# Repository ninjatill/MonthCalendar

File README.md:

# Month Calendar
A daily gold star system, one month at a time. Inspired by the [Every Day Calendar](https://www.kickstarter.com/projects/simonegiertz/the-every-day-calendar), this is a compact version that has 48 total touch pads.

I saw the Every Day Calendar (EDC) referenced on the Particle forums. It sounded like a great idea and I needed way to track if I took my daily allergy pill. However, the EDC is very large and therefore expensive to manufacture. It is also a big challenge (and cost) to read 365 touch inputs and control 365 LEDs (especially if made to be RGB or varying intensity). I also thought the functionality could be expanded beyond just turning an LED on to indicate completion. By the time I got around to designing my own version, the Kickstarter campain had closed and there were no resouces made available via open source yet. So I designed it all from scratch.

My Design Criteria:
- Should be small enough to fit inside a medicine cabinet or mounted on limited wall space in a bathroom.
- Should still be able to track every day of the year.
- Should record and track progress and report it to the cloud for review.
- Should be able to track multiple users (like a husband and wife pair).
- Should use capacitive touch (seems more robust and it's something new to learn).
- Should have colored LEDs that shine up through the PCB (similar to the static LED color on the EDC). Color can be used for:
  - Indicating missed days with red (or some alternative) color.
  - Showing fancy animations to entice interaction/completion.
  - Indicating separate users and tasks via differing color schemes.

Additional considerations (some after starting the design):
- There's no need to have the LEDs on all the time. Perhaps some sort of human presense detector can be incorporated to only turn on the LEDs when someone is near the system.
- If this is in a bathroom, where most people start their day, it would be benificial to act as a calendar to indicate what is the current day.
- Because of the modularity, the top touch plate (described below) could be swapped out for different configurations or locales. It might be a benifit (or neccessary) to add non-volitile storage to the touch plate to identify hardware revisions, serial numbers, locales, layout changes, etc.
- To minimize light bleed between indicators I will fabricate a 3D-printed light collimator.
- Neopixels are the obvious choice for RGB LEDs because they are chainable and have their own internal controller. I think the RGBW chips would be best so you can stil get the white LED "classic" look. Each RGBW Neopixel can draw up to 80 mA and with 48 Neopixels, the max current draw is 3.82 A. If adding day of week indicators, then with 53 Neopixels the current max current draw is up to 4.24 A. Although real-world applications would probably not push more than 2 A, the power draw is still significant and the power supply will have to be chosen appropriately. Additionally, there may have to be firmware constraints in place to prevent over taxing the power supply.

The initial design uses 2 PCBs connected via pin headers. The bottom PCB contains all the controller hardware and LEDs. The Top PCB is merely a touch plate containing all the capacitive touch pads. The microcontroller is inserted on the back-side of the controller PCB as well as the power entry ports. The PCBs will be mounted in a 3D printed case. 

# WARNING: This project is in development!
### Only v0.x files have been uploaded for review and all designs are subject to change without notice.

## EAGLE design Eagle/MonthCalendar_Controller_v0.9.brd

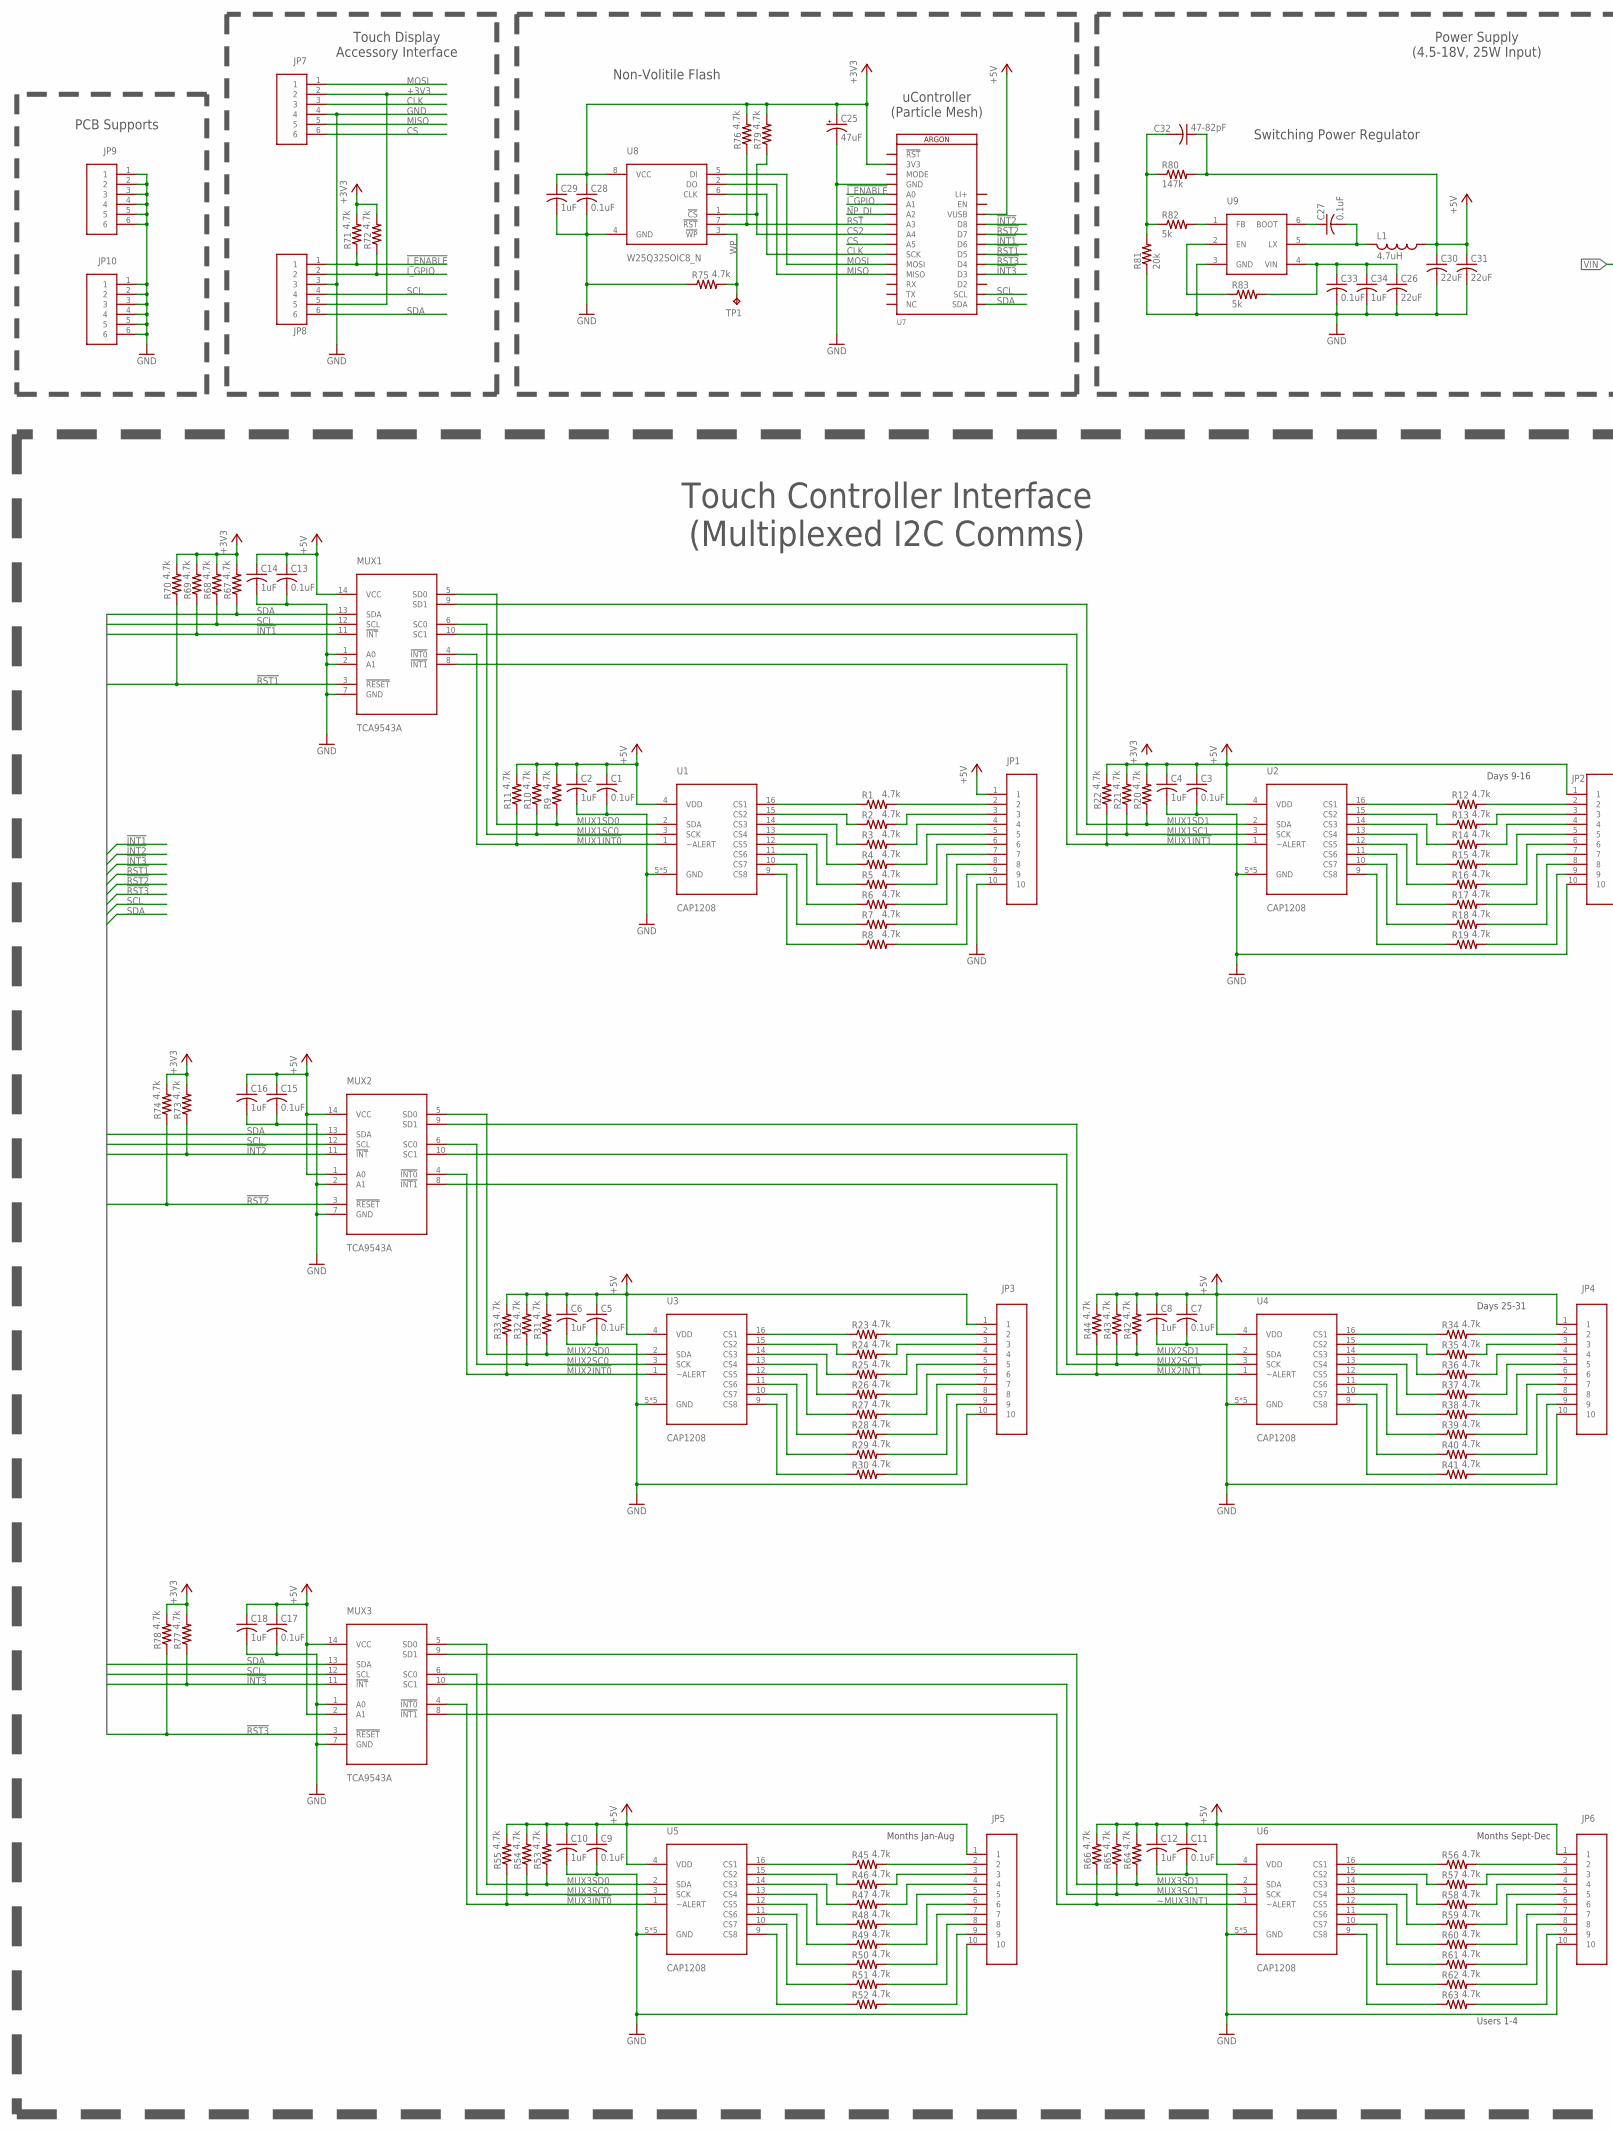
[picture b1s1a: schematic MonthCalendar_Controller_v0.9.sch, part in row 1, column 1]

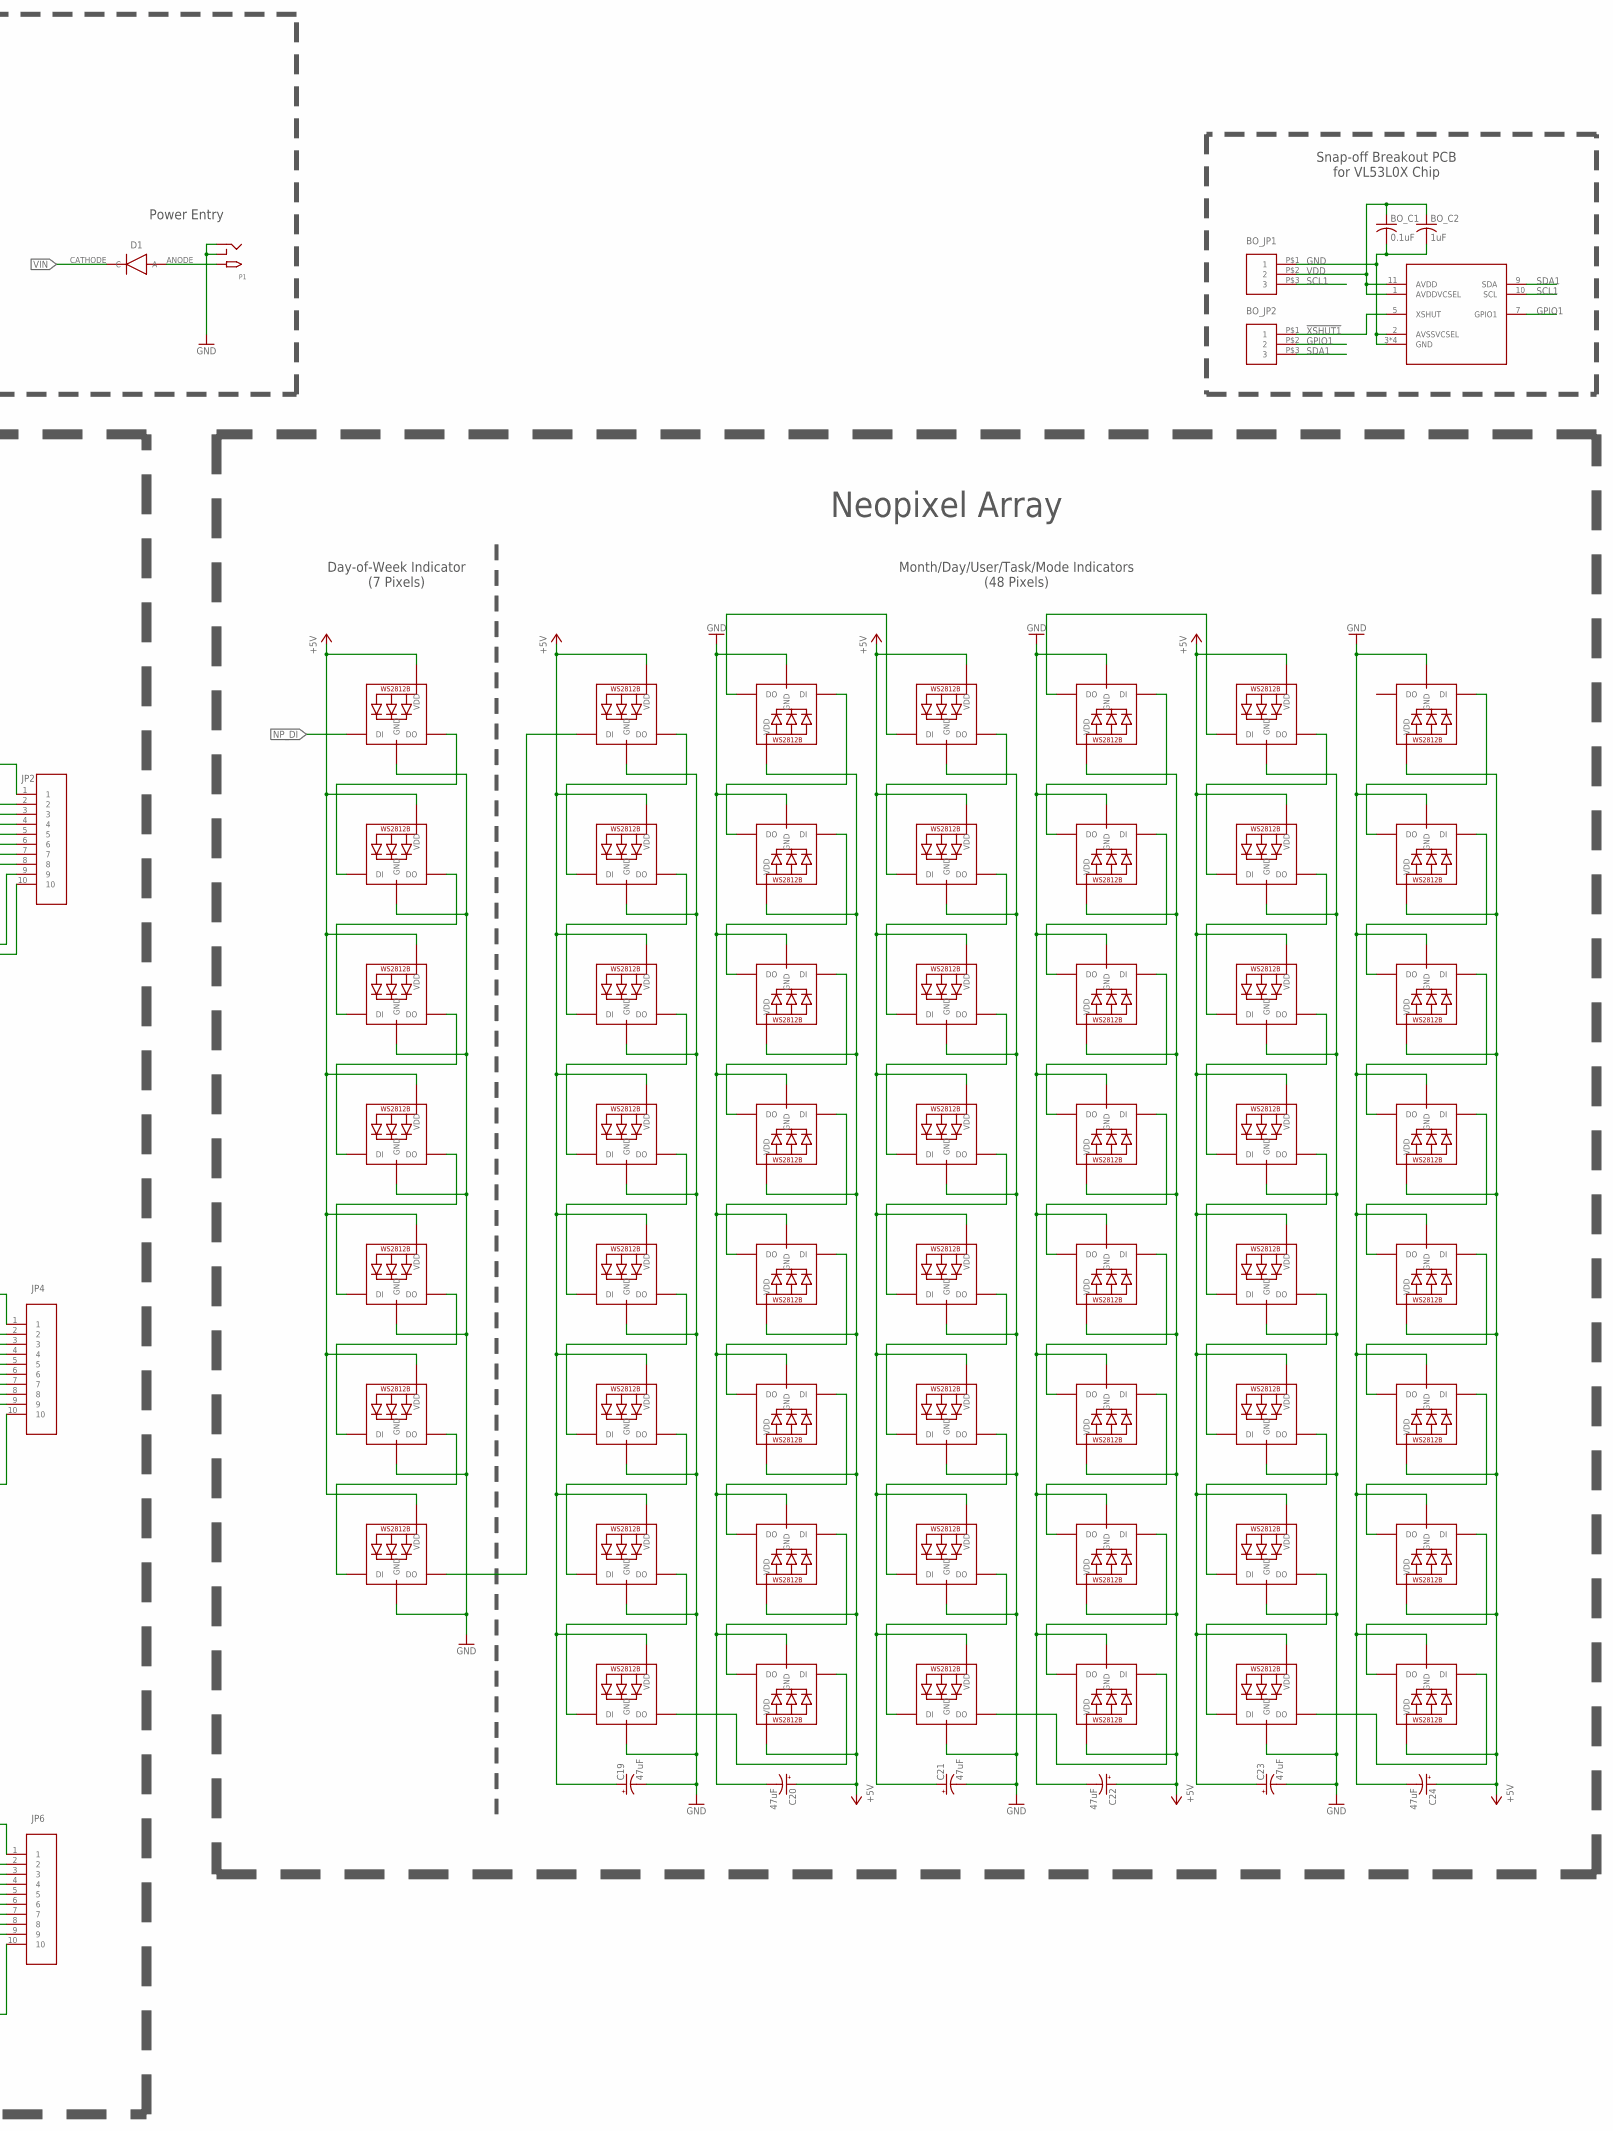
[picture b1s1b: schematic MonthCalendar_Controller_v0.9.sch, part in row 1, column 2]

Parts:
BO_C1: 0.1uF; C0603
BO_C2: 1uF; C0603
BO_JP1, BO_JP2: PINHEAD_1X350MIL; PINHEAD_1X3_50MIL
BO_U1: VL53L0X
C1, C3, C5, C7, C9, C11, C13, C15, C17, C27, C28, C33: 0.1uF; C0603
C2, C4, C6, C8, C10, C12, C14, C16, C18, C29, C34: 1uF; C0603
C19, C20, C21, C22, C23, C24, C25: 47uF; EIA3216
C26, C30, C31: 22uF; C1206
C32: 47-82pF; C0603
D1: DIODE; SOD-128
JP1, JP2, JP3, JP4, JP5, JP6: CON_10POS_1ROWHARWIN_M3531042; CON_PINHEADER_10P_1R_TH_HARWIN_M50-3531042
JP7, JP8, JP9, JP10: CON_6POS_1ROW6P1R_M50_35306; CON_PINHEADER_6P_1R_TH_HARWIN_M50-3530642
L1: 4.7uH; 0207/5V
LED1, LED2, LED3, LED4, LED5, LED6, LED7, LED8, LED9, LED10, LED11, LED12, LED13, LED14, LED15, LED16, LED17, LED18, LED19, LED20, LED21, LED22, LED23, LED24, LED25, LED26, LED27, LED28, LED29, LED30, LED31, LED32, LED33, LED34, LED35, LED36, LED37, LED38, LED39, LED40, LED41, LED42, LED43, LED44, LED45, LED46, LED47, LED48, LED49, LED50, LED51, LED52, LED53, LED54, LED55: WS2812B5050; WS2812B
MUX1, MUX2, MUX3: TCA9543A; TSSOP-14
P1: 2.1MMJACKTHM; PJ-102A
R1, R2, R3, R4, R5, R6, R7, R8, R9, R10, R11, R12, R13, R14, R15, R16, R17, R18, R19, R20, R21, R22, R23, R24, R25, R26, R27, R28, R29, R30, R31, R32, R33, R34, R35, R36, R37, R38, R39, R40, R41, R42, R43, R44, R45, R46, R47, R48, R49, R50, R51, R52, R53, R54, R55, R56, R57, R58, R59, R60, R61, R62, R63, R64, R65, R66, R67, R68, R69, R70, R71, R72, R73, R74, R75, R76, R77, R78, R79: 4.7k; R0603
R80: 147k; R0603
R81: 20k; R0603
R82, R83: 5k; R0603
TP1: TPTP20SQ; TP20SQ
U1, U2, U3, U4, U5, U6: CAP1208; QFN-16-3X3
U7: ARGON
U8: W25Q32SOIC8_N; SOIC-8_NARROW
U9: RT6255AHGJ6FCT-ND; SOT-23-6

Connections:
!INT1: MUX1.11 (!INT), R69.1, U7.23 (D6)
!INT2: MUX2.11 (!INT), R73.1, U7.25 (D8)
!INT3: MUX3.11 (!INT), R77.1, U7.20 (D3)
!I_ENABLE: JP8.1, R71.1, U7.5 (A0)
!MUX1INT0: MUX1.4 (!INT0), R11.1, U1.1 (~ALERT)
!MUX1INT1: MUX1.8 (!INT1), R22.1, U2.1 (~ALERT)
!MUX2INT0: MUX2.4 (!INT0), R33.1, U3.1 (~ALERT)
!MUX2INT1: MUX2.8 (!INT1), R44.1, U4.1 (~ALERT)
!MUX3INT0: MUX3.4 (!INT0), R55.1, U5.1 (~ALERT)
!RST1: MUX1.3 (!RESET), R70.1, U7.22 (D5)
!RST2: MUX2.3 (!RESET), R74.1, U7.24 (D7)
!RST3: MUX3.3 (!RESET), R78.1, U7.21 (D4)
!XSHUT1: BO_JP2.P$1 (1), BO_U1.5 (XSHUT)
+3V3: C25.A (+), C28.1, C29.1, JP7.2, JP8.5, R67.2, R68.2, R69.2, R70.2, R71.2, R72.2, R73.2, R74.2, R76.2, R77.2, R78.2, R79.2, U7.2 (3V3), U8.8 (VCC)
+5V: C1.1, C2.1, C3.1, C4.1, C5.1, C6.1, C7.1, C8.1, C9.1, C10.1, C11.1, C12.1, C13.1, C14.1, C15.1, C16.1, C17.1, C18.1, C19.A (+), C20.A (+), C21.A (+), C22.A (+), C23.A (+), C24.A (+), C30.1, C31.1, C32.1, JP1.1, JP2.1, JP3.1, JP4.1, JP5.1, JP6.1, L1.1, LED1.1-VDD (VDD), LED2.1-VDD (VDD), LED3.1-VDD (VDD), LED4.1-VDD (VDD), LED5.1-VDD (VDD), LED6.1-VDD (VDD), LED7.1-VDD (VDD), LED8.1-VDD (VDD), LED9.1-VDD (VDD), LED10.1-VDD (VDD), LED11.1-VDD (VDD), LED12.1-VDD (VDD), LED13.1-VDD (VDD), LED14.1-VDD (VDD), LED15.1-VDD (VDD), LED16.1-VDD (VDD), LED17.1-VDD (VDD), LED18.1-VDD (VDD), LED19.1-VDD (VDD), LED20.1-VDD (VDD), LED21.1-VDD (VDD), LED22.1-VDD (VDD), LED23.1-VDD (VDD), LED24.1-VDD (VDD), LED25.1-VDD (VDD), LED26.1-VDD (VDD), LED27.1-VDD (VDD), LED28.1-VDD (VDD), LED29.1-VDD (VDD), LED30.1-VDD (VDD), LED31.1-VDD (VDD), LED32.1-VDD (VDD), LED33.1-VDD (VDD), LED34.1-VDD (VDD), LED35.1-VDD (VDD), LED36.1-VDD (VDD), LED37.1-VDD (VDD), LED38.1-VDD (VDD), LED39.1-VDD (VDD), LED40.1-VDD (VDD), LED41.1-VDD (VDD), LED42.1-VDD (VDD), LED43.1-VDD (VDD), LED44.1-VDD (VDD), LED45.1-VDD (VDD), LED46.1-VDD (VDD), LED47.1-VDD (VDD), LED48.1-VDD (VDD), LED49.1-VDD (VDD), LED50.1-VDD (VDD), LED51.1-VDD (VDD), LED52.1-VDD (VDD), LED53.1-VDD (VDD), LED54.1-VDD (VDD), LED55.1-VDD (VDD), MUX1.14 (VCC), MUX2.1 (A0), MUX2.14 (VCC), MUX3.2 (A1), MUX3.14 (VCC), R9.2, R10.2, R11.2, R20.2, R21.2, R22.2, R31.2, R32.2, R33.2, R42.2, R43.2, R44.2, R53.2, R54.2, R55.2, R64.2, R65.2, R66.2, R80.2, U1.4 (VDD), U2.4 (VDD), U3.4 (VDD), U4.4 (VDD), U5.4 (VDD), U6.4 (VDD), U7.26 (VUSB)
BOOT: C27.1, U9.6 (BOOT)
CLK: JP7.3, U7.11 (SCK), U8.6 (CLK)
CS: JP7.6, U7.10 (A5)
CS2: R79.1, U7.9 (A4), U8.1 (!CS)
EN: R83.1, U9.2 (EN)
FB: R82.2, U9.1 (FB)
GND: BO_C1.2, BO_C2.2, BO_JP1.P$1 (1), BO_U1.2 (AVSSVCSEL), BO_U1.3 (GND), BO_U1.4 (GND), BO_U1.6 (GND), BO_U1.12 (GND), C1.2, C2.2, C3.2, C4.2, C5.2, C6.2, C7.2, C8.2, C9.2, C10.2, C11.2, C12.2, C13.2, C14.2, C15.2, C16.2, C17.2, C18.2, C19.C (-), C20.C (-), C21.C (-), C22.C (-), C23.C (-), C24.C (-), C25.C (-), C26.2, C28.2, C29.2, C30.2, C31.2, C33.2, C34.2, JP1.10, JP2.10, JP3.10, JP4.10, JP5.10, JP6.10, JP7.4, JP8.3, JP9.1, JP9.2, JP9.3, JP9.4, JP9.5, JP9.6, JP10.1, JP10.2, JP10.3, JP10.4, JP10.5, JP10.6, LED1.3-GND (GND), LED2.3-GND (GND), LED3.3-GND (GND), LED4.3-GND (GND), LED5.3-GND (GND), LED6.3-GND (GND), LED7.3-GND (GND), LED8.3-GND (GND), LED9.3-GND (GND), LED10.3-GND (GND), LED11.3-GND (GND), LED12.3-GND (GND), LED13.3-GND (GND), LED14.3-GND (GND), LED15.3-GND (GND), LED16.3-GND (GND), LED17.3-GND (GND), LED18.3-GND (GND), LED19.3-GND (GND), LED20.3-GND (GND), LED21.3-GND (GND), LED22.3-GND (GND), LED23.3-GND (GND), LED24.3-GND (GND), LED25.3-GND (GND), LED26.3-GND (GND), LED27.3-GND (GND), LED28.3-GND (GND), LED29.3-GND (GND), LED30.3-GND (GND), LED31.3-GND (GND), LED32.3-GND (GND), LED33.3-GND (GND), LED34.3-GND (GND), LED35.3-GND (GND), LED36.3-GND (GND), LED37.3-GND (GND), LED38.3-GND (GND), LED39.3-GND (GND), LED40.3-GND (GND), LED41.3-GND (GND), LED42.3-GND (GND), LED43.3-GND (GND), LED44.3-GND (GND), LED45.3-GND (GND), LED46.3-GND (GND), LED47.3-GND (GND), LED48.3-GND (GND), LED49.3-GND (GND), LED50.3-GND (GND), LED51.3-GND (GND), LED52.3-GND (GND), LED53.3-GND (GND), LED54.3-GND (GND), LED55.3-GND (GND), MUX1.1 (A0), MUX1.2 (A1), MUX1.7 (GND), MUX2.2 (A1), MUX2.7 (GND), MUX3.1 (A0), MUX3.7 (GND), P1.RING, P1.RING_SW, R75.1, R81.1, U1.5 (GND), U1.6 (GND), U1.7 (GND), U1.8 (GND), U1.PAD (GND), U2.5 (GND), U2.6 (GND), U2.7 (GND), U2.8 (GND), U2.PAD (GND), U3.5 (GND), U3.6 (GND), U3.7 (GND), U3.8 (GND), U3.PAD (GND), U4.5 (GND), U4.6 (GND), U4.7 (GND), U4.8 (GND), U4.PAD (GND), U5.5 (GND), U5.6 (GND), U5.7 (GND), U5.8 (GND), U5.PAD (GND), U6.5 (GND), U6.6 (GND), U6.7 (GND), U6.8 (GND), U6.PAD (GND), U7.4 (GND), U8.4 (GND), U9.3 (GND)
GPIO1: BO_JP2.P$2 (2), BO_U1.7 (GPIO1)
I_GPIO: JP8.2, R72.1, U7.6 (A1)
LI+: U7.28 (LI+)
LX: C27.2, L1.2, U9.5 (LX)
MISO: JP7.5, U7.13 (MISO), U8.2 (DO)
MOSI: JP7.1, U7.12 (MOSI), U8.5 (DI)
MUX1SC0: MUX1.6 (SC0), R10.1, U1.3 (SCK)
MUX1SC1: MUX1.10 (SC1), R21.1, U2.3 (SCK)
MUX1SD0: MUX1.5 (SD0), R9.1, U1.2 (SDA)
MUX1SD1: MUX1.9 (SD1), R20.1, U2.2 (SDA)
MUX2SC0: MUX2.6 (SC0), R32.1, U3.3 (SCK)
MUX2SC1: MUX2.10 (SC1), R43.1, U4.3 (SCK)
MUX2SD0: MUX2.5 (SD0), R31.1, U3.2 (SDA)
MUX2SD1: MUX2.9 (SD1), R42.1, U4.2 (SDA)
MUX3SC0: MUX3.6 (SC0), R54.1, U5.3 (SCK)
MUX3SC1: MUX3.10 (SC1), R65.1, U6.3 (SCK)
MUX3SD0: MUX3.5 (SD0), R53.1, U5.2 (SDA)
MUX3SD1: MUX3.9 (SD1), R64.1, U6.2 (SDA)
unnamed: R1.1, U1.16 (CS1)
unnamed: JP1.2, R1.2
unnamed: JP1.3, R2.2
unnamed: R2.1, U1.15 (CS2)
unnamed: R3.1, U1.14 (CS3)
unnamed: R4.1, U1.13 (CS4)
unnamed: R5.1, U1.12 (CS5)
unnamed: R6.1, U1.11 (CS6)
unnamed: R7.1, U1.10 (CS7)
unnamed: R8.1, U1.9 (CS8)
unnamed: JP1.4, R3.2
unnamed: R12.1, U2.16 (CS1)
unnamed: R13.1, U2.15 (CS2)
unnamed: R14.1, U2.14 (CS3)
unnamed: R15.1, U2.13 (CS4)
unnamed: R16.1, U2.12 (CS5)
unnamed: R17.1, U2.11 (CS6)
unnamed: R18.1, U2.10 (CS7)
unnamed: R19.1, U2.9 (CS8)
unnamed: JP2.2, R12.2
unnamed: JP1.5, R4.2
unnamed: JP1.6, R5.2
unnamed: JP1.7, R6.2
unnamed: JP1.8, R7.2
unnamed: JP1.9, R8.2
unnamed: LED1.2-DOUT (DO), LED2.4-DIN (DI)
unnamed: LED2.2-DOUT (DO), LED3.4-DIN (DI)
unnamed: LED3.2-DOUT (DO), LED4.4-DIN (DI)
unnamed: JP2.3, R13.2
unnamed: JP2.4, R14.2
unnamed: JP2.5, R15.2
unnamed: JP2.6, R16.2
unnamed: JP2.7, R17.2
unnamed: JP2.8, R18.2
unnamed: JP2.9, R19.2
unnamed: LED4.2-DOUT (DO), LED5.4-DIN (DI)
unnamed: LED5.2-DOUT (DO), LED6.4-DIN (DI)
unnamed: LED6.2-DOUT (DO), LED7.4-DIN (DI)
unnamed: R23.1, U3.16 (CS1)
unnamed: R24.1, U3.15 (CS2)
unnamed: R25.1, U3.14 (CS3)
unnamed: R26.1, U3.13 (CS4)
unnamed: R27.1, U3.12 (CS5)
unnamed: R28.1, U3.11 (CS6)
unnamed: R29.1, U3.10 (CS7)
unnamed: R30.1, U3.9 (CS8)
unnamed: JP3.2, R23.2
unnamed: JP3.3, R24.2
unnamed: JP3.4, R25.2
unnamed: JP3.5, R26.2
unnamed: JP3.6, R27.2
unnamed: JP3.7, R28.2
unnamed: JP3.8, R29.2
unnamed: JP3.9, R30.2
unnamed: LED7.2-DOUT (DO), LED8.4-DIN (DI)
unnamed: LED9.2-DOUT (DO), LED10.4-DIN (DI)
unnamed: LED10.2-DOUT (DO), LED11.4-DIN (DI)
unnamed: R34.1, U4.16 (CS1)
unnamed: R35.1, U4.15 (CS2)
unnamed: R36.1, U4.14 (CS3)
unnamed: R37.1, U4.13 (CS4)
unnamed: R38.1, U4.12 (CS5)
unnamed: R39.1, U4.11 (CS6)
unnamed: R40.1, U4.10 (CS7)
unnamed: R41.1, U4.9 (CS8)
unnamed: JP4.2, R34.2
unnamed: JP4.3, R35.2
unnamed: JP4.4, R36.2
unnamed: JP4.5, R37.2
unnamed: JP4.6, R38.2
unnamed: JP4.7, R39.2
unnamed: JP4.8, R40.2
unnamed: JP4.9, R41.2
unnamed: LED11.2-DOUT (DO), LED12.4-DIN (DI)
unnamed: LED12.2-DOUT (DO), LED13.4-DIN (DI)
unnamed: LED13.2-DOUT (DO), LED14.4-DIN (DI)
unnamed: R45.1, U5.16 (CS1)
unnamed: R46.1, U5.15 (CS2)
unnamed: R47.1, U5.14 (CS3)
unnamed: R48.1, U5.13 (CS4)
unnamed: R49.1, U5.12 (CS5)
unnamed: R50.1, U5.11 (CS6)
unnamed: R51.1, U5.10 (CS7)
unnamed: R52.1, U5.9 (CS8)
unnamed: JP5.2, R45.2
unnamed: JP5.3, R46.2
unnamed: JP5.4, R47.2
unnamed: JP5.5, R48.2
unnamed: JP5.6, R49.2
unnamed: JP5.7, R50.2
unnamed: JP5.8, R51.2
unnamed: JP5.9, R52.2
unnamed: LED14.2-DOUT (DO), LED15.4-DIN (DI)
unnamed: LED15.2-DOUT (DO), LED16.4-DIN (DI)
unnamed: LED17.2-DOUT (DO), LED18.4-DIN (DI)
unnamed: R56.1, U6.16 (CS1)
unnamed: R57.1, U6.15 (CS2)
unnamed: R58.1, U6.14 (CS3)
unnamed: R59.1, U6.13 (CS4)
unnamed: R60.1, U6.12 (CS5)
unnamed: R61.1, U6.11 (CS6)
unnamed: R62.1, U6.10 (CS7)
unnamed: R63.1, U6.9 (CS8)
unnamed: JP6.2, R56.2
unnamed: JP6.3, R57.2
unnamed: JP6.4, R58.2
unnamed: JP6.5, R59.2
unnamed: JP6.6, R60.2
unnamed: JP6.7, R61.2
unnamed: JP6.8, R62.2
unnamed: JP6.9, R63.2
unnamed: LED18.2-DOUT (DO), LED19.4-DIN (DI)
unnamed: LED19.2-DOUT (DO), LED20.4-DIN (DI)
unnamed: LED20.2-DOUT (DO), LED21.4-DIN (DI)
unnamed: LED21.2-DOUT (DO), LED22.4-DIN (DI)
unnamed: LED22.2-DOUT (DO), LED23.4-DIN (DI)
unnamed: LED23.2-DOUT (DO), LED24.4-DIN (DI)
unnamed: LED25.2-DOUT (DO), LED26.4-DIN (DI)
unnamed: LED26.2-DOUT (DO), LED27.4-DIN (DI)
unnamed: LED27.2-DOUT (DO), LED28.4-DIN (DI)
unnamed: LED28.2-DOUT (DO), LED29.4-DIN (DI)
unnamed: LED29.2-DOUT (DO), LED30.4-DIN (DI)
unnamed: LED30.2-DOUT (DO), LED31.4-DIN (DI)
unnamed: LED31.2-DOUT (DO), LED32.4-DIN (DI)
unnamed: LED33.2-DOUT (DO), LED34.4-DIN (DI)
unnamed: LED34.2-DOUT (DO), LED35.4-DIN (DI)
unnamed: LED35.2-DOUT (DO), LED36.4-DIN (DI)
unnamed: LED36.2-DOUT (DO), LED37.4-DIN (DI)
unnamed: LED37.2-DOUT (DO), LED38.4-DIN (DI)
unnamed: LED38.2-DOUT (DO), LED39.4-DIN (DI)
unnamed: LED39.2-DOUT (DO), LED40.4-DIN (DI)
unnamed: LED41.2-DOUT (DO), LED42.4-DIN (DI)
unnamed: LED42.2-DOUT (DO), LED43.4-DIN (DI)
unnamed: LED43.2-DOUT (DO), LED44.4-DIN (DI)
unnamed: LED44.2-DOUT (DO), LED45.4-DIN (DI)
unnamed: LED45.2-DOUT (DO), LED46.4-DIN (DI)
unnamed: LED46.2-DOUT (DO), LED47.4-DIN (DI)
unnamed: LED47.2-DOUT (DO), LED48.4-DIN (DI)
unnamed: LED8.2-DOUT (DO), LED9.4-DIN (DI)
unnamed: LED24.2-DOUT (DO), LED25.4-DIN (DI)
unnamed: LED40.2-DOUT (DO), LED41.4-DIN (DI)
unnamed: LED16.2-DOUT (DO), LED17.4-DIN (DI)
unnamed: LED32.2-DOUT (DO), LED33.4-DIN (DI)
unnamed: LED49.2-DOUT (DO), LED50.4-DIN (DI)
unnamed: LED50.2-DOUT (DO), LED51.4-DIN (DI)
unnamed: LED51.2-DOUT (DO), LED52.4-DIN (DI)
unnamed: LED52.2-DOUT (DO), LED53.4-DIN (DI)
unnamed: LED53.2-DOUT (DO), LED54.4-DIN (DI)
unnamed: LED54.2-DOUT (DO), LED55.4-DIN (DI)
unnamed: LED1.4-DIN (DI), LED55.2-DOUT (DO)
unnamed: C32.2, R80.1, R81.2, R82.1
NP_DI: LED49.4-DIN (DI), U7.7 (A2)
RST: R76.1, U7.8 (A3), U8.7 (!RST)
SCL: JP8.4, MUX1.12 (SCL), MUX2.12 (SCL), MUX3.12 (SCL), R68.1, U7.18 (SCL)
SCL1: BO_JP1.P$3 (3), BO_U1.10 (SCL)
SDA: JP8.6, MUX1.13 (SDA), MUX2.13 (SDA), MUX3.13 (SDA), R67.1, U7.17 (SDA)
SDA1: BO_JP2.P$3 (3), BO_U1.9 (SDA)
VDD: BO_C1.1, BO_C2.1, BO_JP1.P$2 (2), BO_U1.1 (AVDDVCSEL), BO_U1.11 (AVDD)
VIN: C26.1, C33.1, C34.1, D1.CATHODE (C), R83.2, U9.4 (VIN)
VPORT: D1.ANODE (A), P1.TIP
WP: R75.2, TP1.TP, U8.3 (!WP)
~MUX3INT1: MUX3.8 (!INT1), R66.1, U6.1 (~ALERT)

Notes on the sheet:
Days 9-16
Days 25-31
Months Jan-Aug
Months Sept-Dec
Users 1-4
Power Entry
uController (Particle Mesh)
Touch Display Accessory Interface
Snap-off Breakout PCB for VL53L0X Chip
Neopixel Array
Day-of-Week Indicator (7 Pixels)
Month/Day/User/Task/Mode Indicators (48 Pixels)
Touch Controller Interface (Multiplexed I2C Comms)
Non-Volitile Flash
PCB Supports
Switching Power Regulator
Power Supply (4.5-18V, 25W Input)

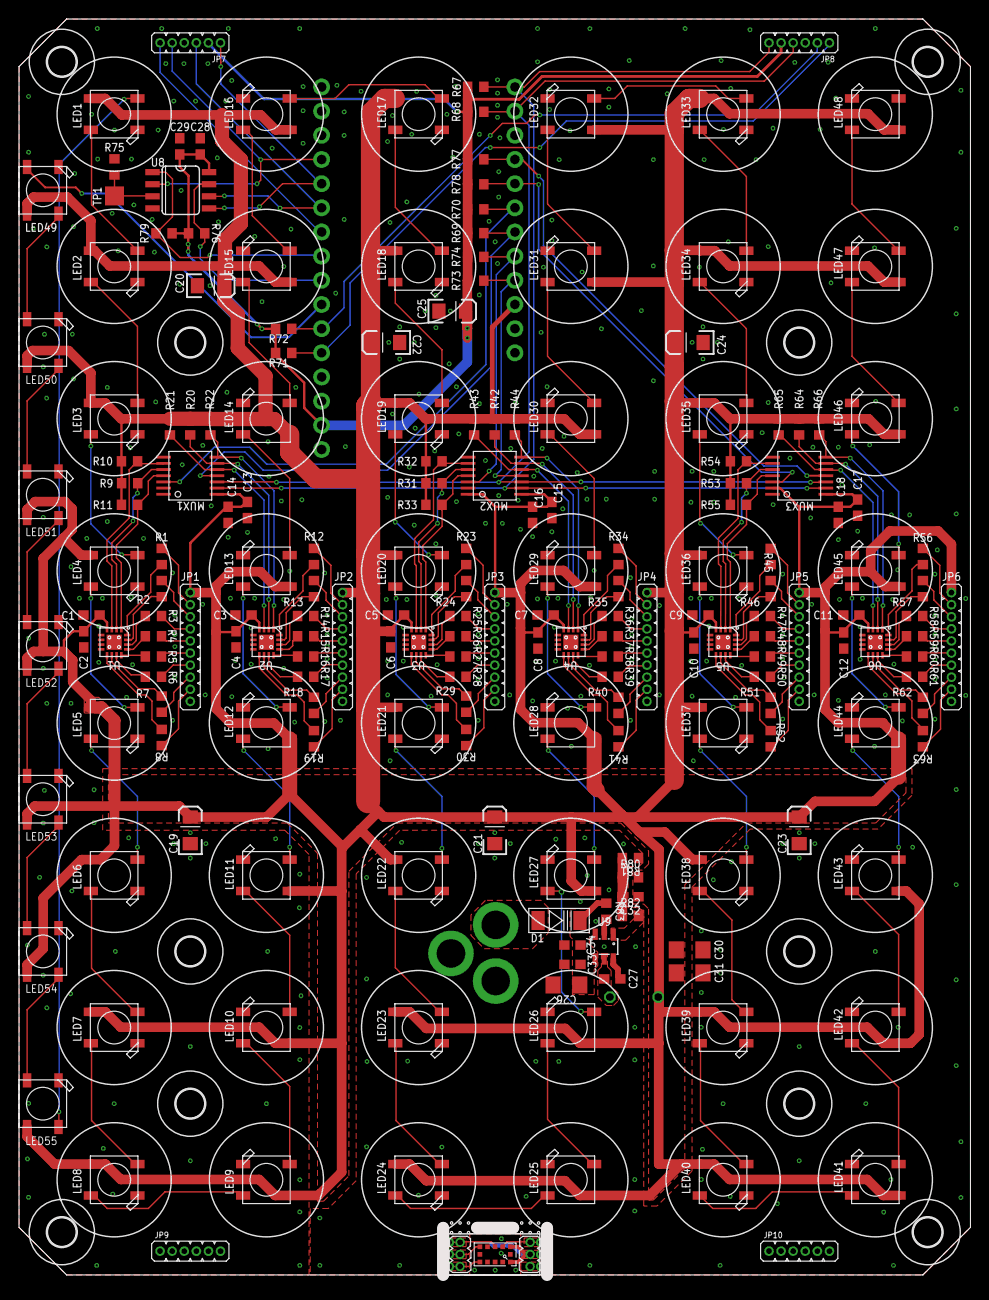
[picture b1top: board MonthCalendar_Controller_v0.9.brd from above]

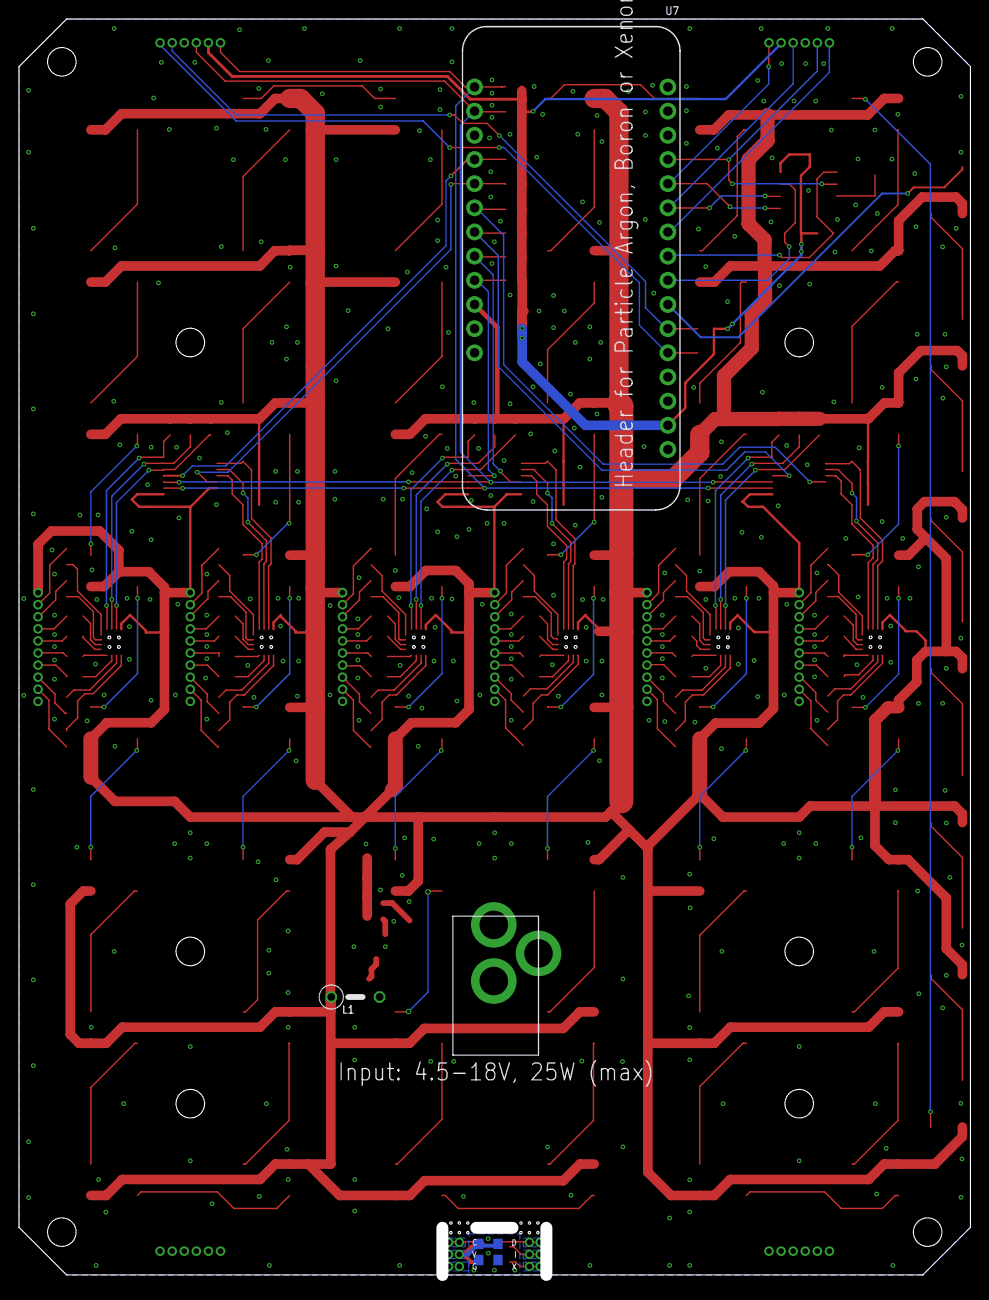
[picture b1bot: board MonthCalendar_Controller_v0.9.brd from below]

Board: 2 copper layers, 100.0 x 132.0 mm, 261 parts (5 on the bottom side), 201 nets.

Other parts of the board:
U$1, U$2, U$3, U$4, U$5, U$6, U$7, U$8, U$9, U$10, U$11, U$12, U$13, U$14, U$15, U$16, U$17, U$18, U$19, U$20, U$21, U$22, U$23, U$24, U$25, U$26, U$27, U$28, U$29, U$30, U$31, U$32, U$33, U$34, U$35, U$36, U$37, U$38, U$39, U$40, U$41, U$42, U$43, U$44, U$45, U$46, U$47, U$48: PAD_CAPACITIVETOUCH_2_OUTLINE
U$49, U$50, U$51, U$52, U$53, U$54, U$55, U$56, U$57, U$58: 3,0

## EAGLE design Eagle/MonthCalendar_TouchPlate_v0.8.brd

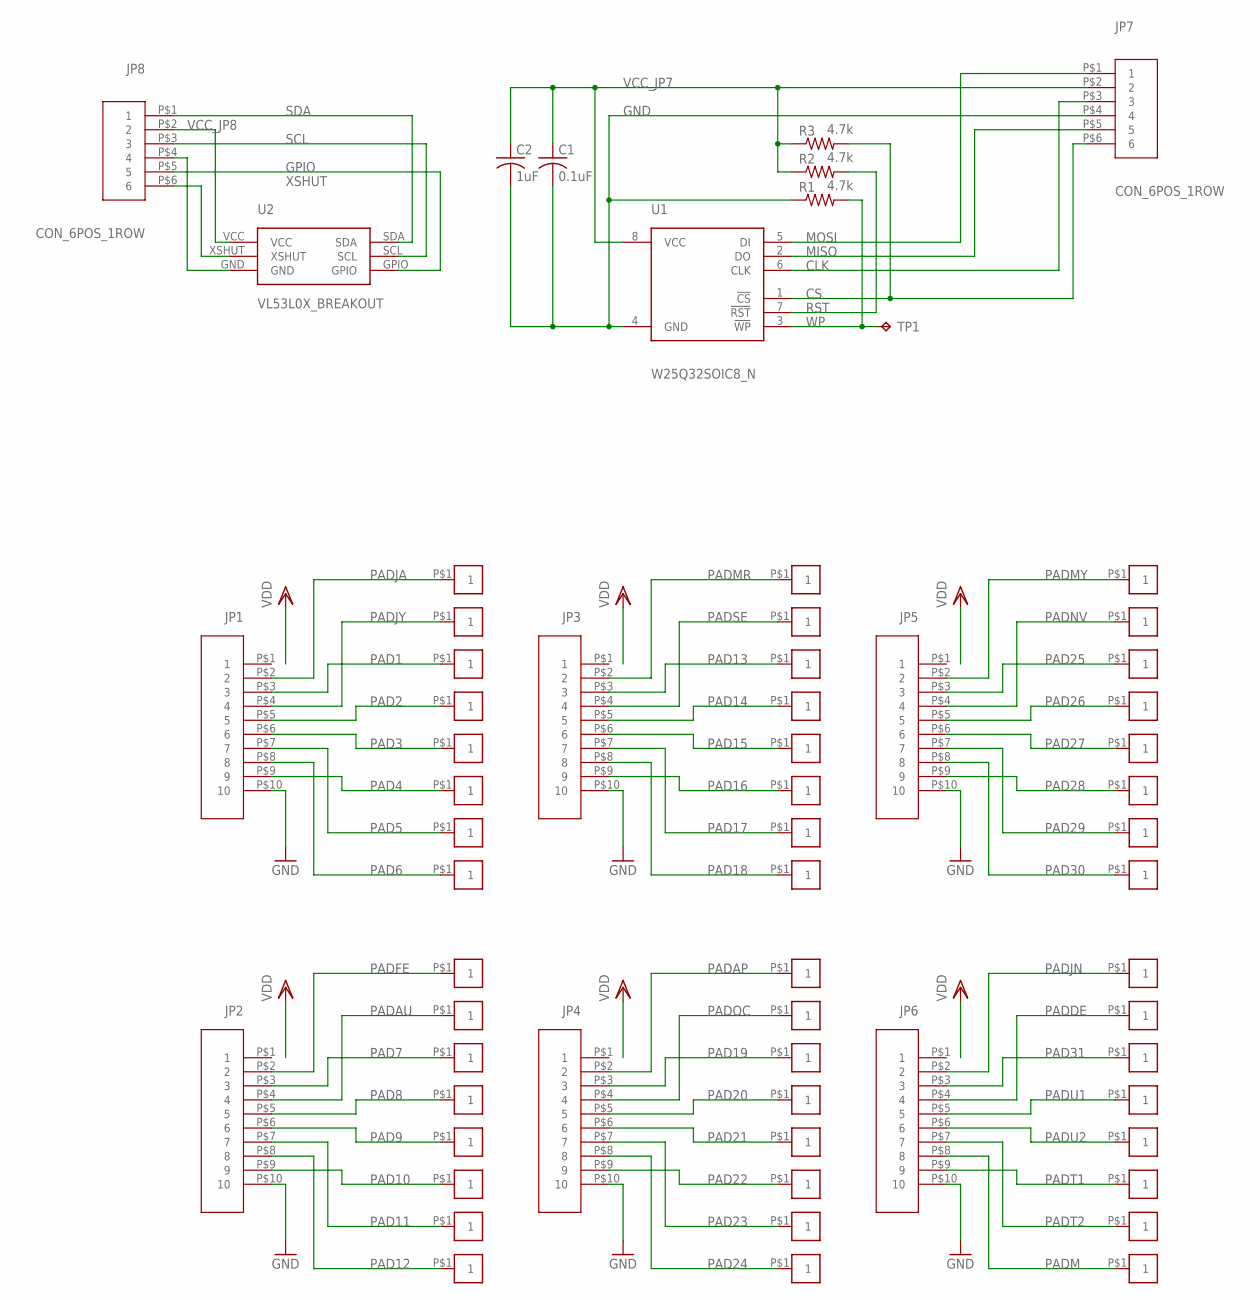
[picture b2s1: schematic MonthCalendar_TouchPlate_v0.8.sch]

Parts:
C1: 0.1uF; C0603
C2: 1uF; C0603
JP1, JP2, JP3, JP4, JP5, JP6: CON_10POS_1ROWHARWIN_M50-3141045_N; CON_RECPT_10P_1R_SMD_HARWIN_M50-3141045_NARROW
JP7, JP8: CON_6POS_1ROW; CON_RECPT_6P_1R_SMD_HARWIN_M50-3141045_NARROW
R1, R2, R3: 4.7k; R0603
TP1: TPTP20SQ; TP20SQ
U1: W25Q32SOIC8_N; SOIC-8_NARROW
U2: VL53L0X_BREAKOUT; VL53L0X_BREAKOUT_THROUGHPCB
U$1, U$2, U$3, U$4, U$5, U$6, U$7, U$8, U$9, U$10, U$11, U$12, U$13, U$14, U$15, U$16, U$17, U$18, U$19, U$20, U$21, U$22, U$23, U$24, U$25, U$26, U$27, U$28, U$29, U$30, U$31, U$32, U$33, U$34, U$35, U$36, U$37, U$38, U$39, U$40, U$41, U$42, U$43, U$44, U$45, U$46, U$47, U$48: PAD_CAPACITIVETOUCHV4; PAD_CAPACITIVETOUCH_4

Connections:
CLK: JP7.P$3 (3), U1.6 (CLK)
CS: JP7.P$6 (6), R3.2, U1.1 (!CS)
GND: C1.2, C2.2, JP1.P$10 (10), JP2.P$10 (10), JP3.P$10 (10), JP4.P$10 (10), JP5.P$10 (10), JP6.P$10 (10), JP7.P$4 (4), JP8.P$4 (4), R1.1, U1.4 (GND), U2.GND
GPIO: JP8.P$5 (5), U2.GPIO
MISO: JP7.P$5 (5), U1.2 (DO)
MOSI: JP7.P$1 (1), U1.5 (DI)
PAD1: JP1.P$3 (3), U$3.P$1
PAD2: JP1.P$5 (5), U$4.P$1
PAD3: JP1.P$6 (6), U$5.P$1
PAD4: JP1.P$9 (9), U$6.P$1
PAD5: JP1.P$7 (7), U$7.P$1
PAD6: JP1.P$8 (8), U$8.P$1
PAD7: JP2.P$3 (3), U$11.P$1
PAD8: JP2.P$5 (5), U$12.P$1
PAD9: JP2.P$6 (6), U$13.P$1
PAD10: JP2.P$9 (9), U$14.P$1
PAD11: JP2.P$7 (7), U$15.P$1
PAD12: JP2.P$8 (8), U$16.P$1
PAD13: JP3.P$3 (3), U$19.P$1
PAD14: JP3.P$5 (5), U$20.P$1
PAD15: JP3.P$6 (6), U$21.P$1
PAD16: JP3.P$9 (9), U$22.P$1
PAD17: JP3.P$7 (7), U$23.P$1
PAD18: JP3.P$8 (8), U$24.P$1
PAD19: JP4.P$3 (3), U$27.P$1
PAD20: JP4.P$5 (5), U$28.P$1
PAD21: JP4.P$6 (6), U$29.P$1
PAD22: JP4.P$9 (9), U$30.P$1
PAD23: JP4.P$7 (7), U$31.P$1
PAD24: JP4.P$8 (8), U$32.P$1
PAD25: JP5.P$3 (3), U$35.P$1
PAD26: JP5.P$5 (5), U$36.P$1
PAD27: JP5.P$6 (6), U$37.P$1
PAD28: JP5.P$9 (9), U$38.P$1
PAD29: JP5.P$7 (7), U$39.P$1
PAD30: JP5.P$8 (8), U$40.P$1
PAD31: JP6.P$3 (3), U$43.P$1
PADAP: JP4.P$2 (2), U$25.P$1
PADAU: JP2.P$4 (4), U$10.P$1
PADDE: JP6.P$4 (4), U$42.P$1
PADFE: JP2.P$2 (2), U$9.P$1
PADJA: JP1.P$2 (2), U$1.P$1
PADJN: JP6.P$2 (2), U$41.P$1
PADJY: JP1.P$4 (4), U$2.P$1
PADM: JP6.P$8 (8), U$48.P$1
PADMR: JP3.P$2 (2), U$17.P$1
PADMY: JP5.P$2 (2), U$33.P$1
PADNV: JP5.P$4 (4), U$34.P$1
PADOC: JP4.P$4 (4), U$26.P$1
PADSE: JP3.P$4 (4), U$18.P$1
PADT1: JP6.P$9 (9), U$46.P$1
PADT2: JP6.P$7 (7), U$47.P$1
PADU1: JP6.P$5 (5), U$44.P$1
PADU2: JP6.P$6 (6), U$45.P$1
RST: R2.2, U1.7 (!RST)
SCL: JP8.P$3 (3), U2.SCL
SDA: JP8.P$1 (1), U2.SDA
VCC_JP7: C1.1, C2.1, JP7.P$2 (2), R2.1, R3.1, U1.8 (VCC)
VCC_JP8: JP8.P$2 (2), U2.VCC
WP: R1.2, TP1.TP, U1.3 (!WP)
XSHUT: JP8.P$6 (6), U2.XSHUT

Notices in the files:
parts and their libraries:
Particle-Devices: Licensing: Designed by Particle.
